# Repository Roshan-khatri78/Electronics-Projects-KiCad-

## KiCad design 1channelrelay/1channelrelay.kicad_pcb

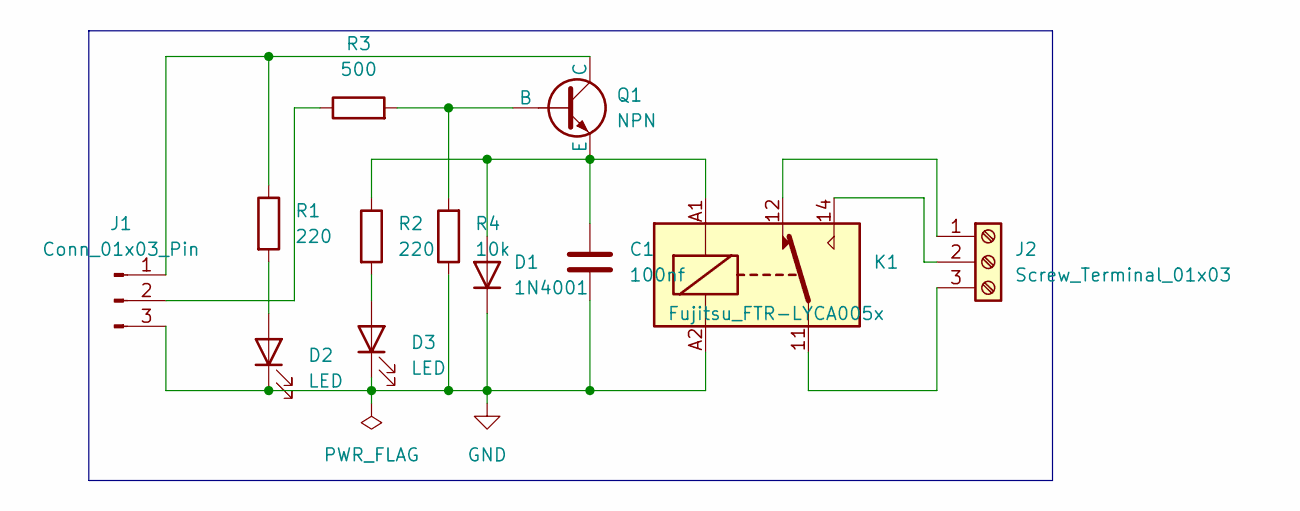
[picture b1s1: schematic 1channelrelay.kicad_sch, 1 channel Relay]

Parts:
C1: 100nf; C_0201_0603Metric
D1: 1N4001; D_0201_0603Metric
D2, D3: LED; LED_0201_0603Metric
J1: Conn_01x03_Pin; PinHeader_1x03_P1.00mm_Horizontal
J2: Screw_Terminal_01x03; TerminalBlock_RND_205-00013_1x03_P5.00mm_Horizontal
K1: Fujitsu_FTR-LYCA005x; Relay_SPDT_Finder_36.11
Q1: NPN; SOT-23
R1, R2: 220; R_0201_0603Metric
R3: 500; R_0201_0603Metric
R4: 10k; R_0201_0603Metric

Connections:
GND: C1.2, D1.1 (K), D2.1 (K), D3.1 (K), J1.3, K1.A2, R4.1; also elsewhere on the board
unnamed: C1.1, D1.2 (A), K1.A1, Q1.3 (E), R2.1
unnamed: D2.2 (A), R1.2
unnamed: D3.2 (A), R2.2
unnamed 4: J1.1, Q1.1 (C), R1.1; also elsewhere on the board
unnamed 5: J1.2, R3.1; also elsewhere on the board
unnamed: J2.1, K1.12
unnamed: J2.2, K1.14
unnamed: J2.3, K1.11
unnamed: Q1.2 (B), R3.2, R4.2

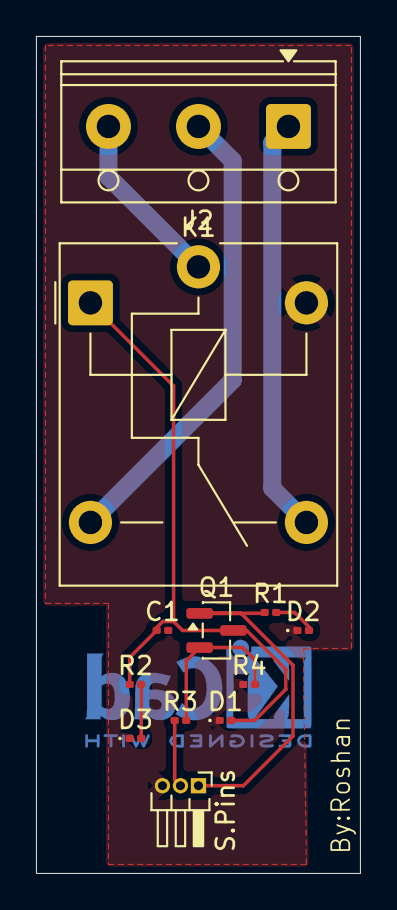
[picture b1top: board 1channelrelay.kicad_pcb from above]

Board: 2 copper layers, 18.0 x 46.5 mm, 12 parts (0 on the bottom side), 10 nets.

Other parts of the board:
S.Pins: Conn_01x03_Pin; PinHeader_1x03_P1.00mm_Horizontal

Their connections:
GND: S.Pins.3; also elsewhere on the board
unnamed 4: S.Pins.1; also elsewhere on the board
unnamed 5: S.Pins.2; also elsewhere on the board

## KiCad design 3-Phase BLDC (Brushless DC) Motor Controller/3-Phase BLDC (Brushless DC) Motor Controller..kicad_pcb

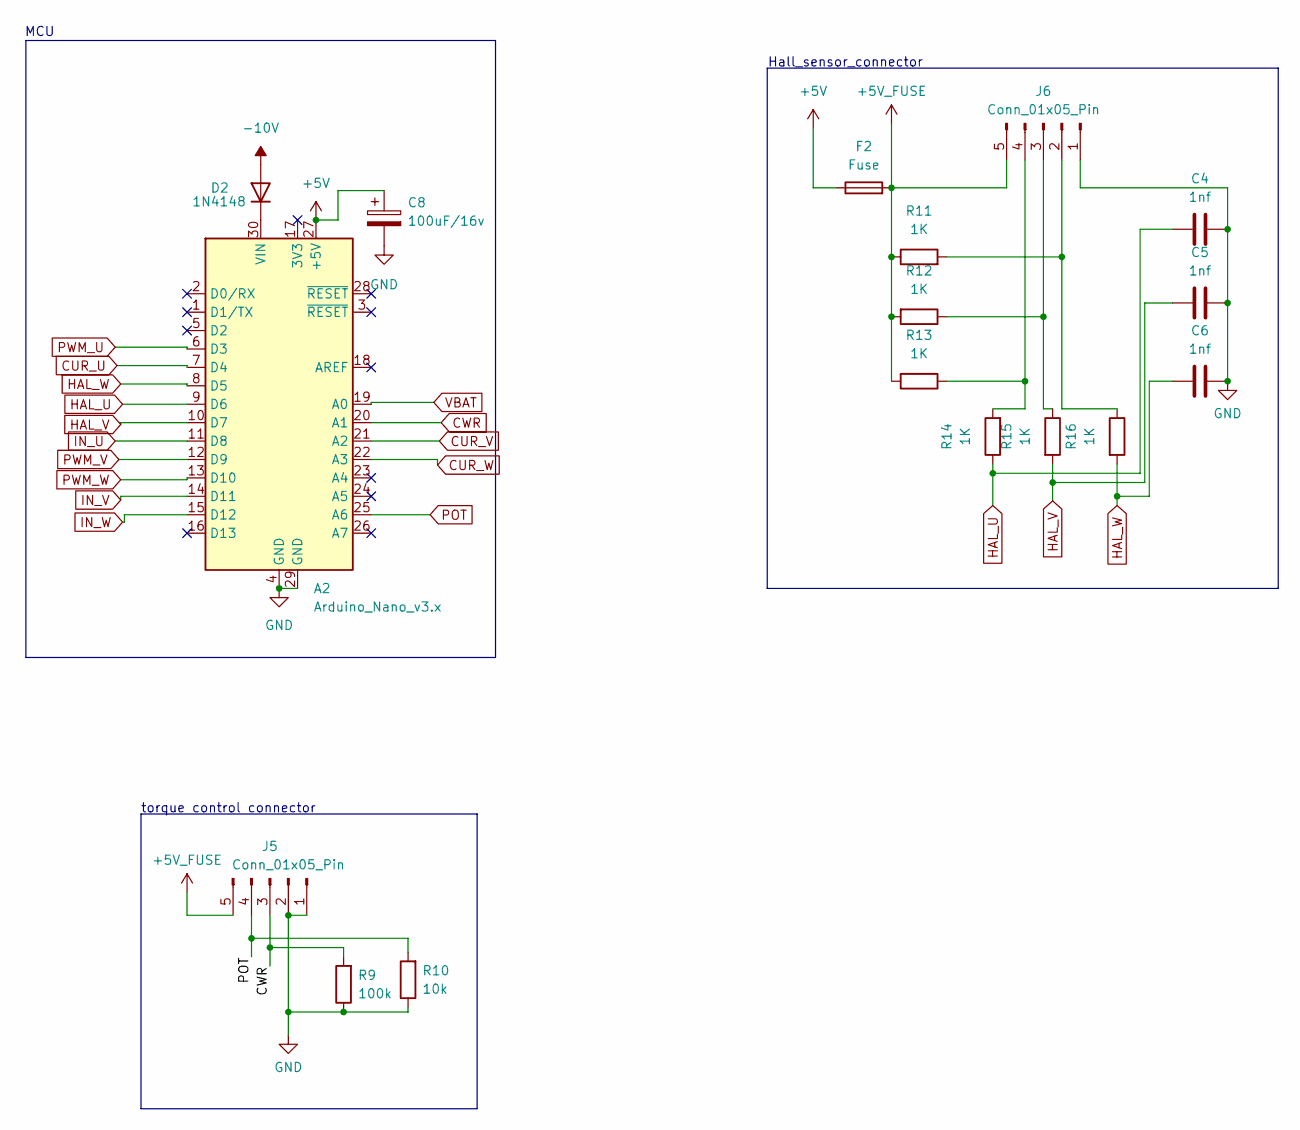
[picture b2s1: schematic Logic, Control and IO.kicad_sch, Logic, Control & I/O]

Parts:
A2: Arduino_Nano_v3.x; Arduino_Nano
C4, C5, C6: 1nf; C_Disc_D5.0mm_W2.5mm_P2.50mm
C8: 100uF/16v; CP_Radial_D5.0mm_P2.50mm
D2: 1N4148; D_DO-35_SOD27_P7.62mm_Horizontal
F2: Fuse; Fuse_2010_5025Metric
J5, J6: Conn_01x05_Pin; PinHeader_1x05_P2.54mm_Vertical
R9: 100k; R_Axial_DIN0204_L3.6mm_D1.6mm_P5.08mm_Horizontal
R10: 10k; R_Axial_DIN0204_L3.6mm_D1.6mm_P5.08mm_Horizontal
R11, R12, R13, R14, R15, R16: 1K; R_Axial_DIN0204_L3.6mm_D1.6mm_P5.08mm_Horizontal

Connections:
+5V: A2.27 (+5V), C8.1, F2.1; also elsewhere on the board
+5V_FUSE: F2.2, J5.5, J6.5, R11.1, R12.2, R13.2
-10V: D2.2 (A); also elsewhere on the board
CUR_U: A2.7 (D4); also elsewhere on the board
CUR_V: A2.21 (A2); also elsewhere on the board
CUR_W: A2.22 (A3); also elsewhere on the board
CWR: A2.20 (A1), J5.3, R9.2
GND: A2.4 (GND), A2.29 (GND), C4.2, C5.2, C6.2, C8.2, J5.1, J5.2, J6.1, R9.1, R10.1; also elsewhere on the board
HAL_U: A2.9 (D6), C4.1, R14.1
HAL_V: A2.10 (D7), C5.1, R15.2
HAL_W: A2.8 (D5), C6.1, R16.2
IN_U: A2.11 (D8); also elsewhere on the board
IN_V: A2.14 (D11); also elsewhere on the board
IN_W: A2.15 (D12); also elsewhere on the board
unnamed: A2.30 (VIN), D2.1 (K)
unnamed: J6.2, R11.2, R16.1
unnamed: J6.3, R12.1, R15.1
unnamed: J6.4, R13.1, R14.2
POT: A2.25 (A6), J5.4, R10.2
PWM_U: A2.6 (D3); also elsewhere on the board
PWM_V: A2.12 (D9); also elsewhere on the board
PWM_W: A2.13 (D10); also elsewhere on the board
VBAT: A2.19 (A0); also elsewhere on the board

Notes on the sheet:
torque control connector
MCU
Hall_sensor_connector

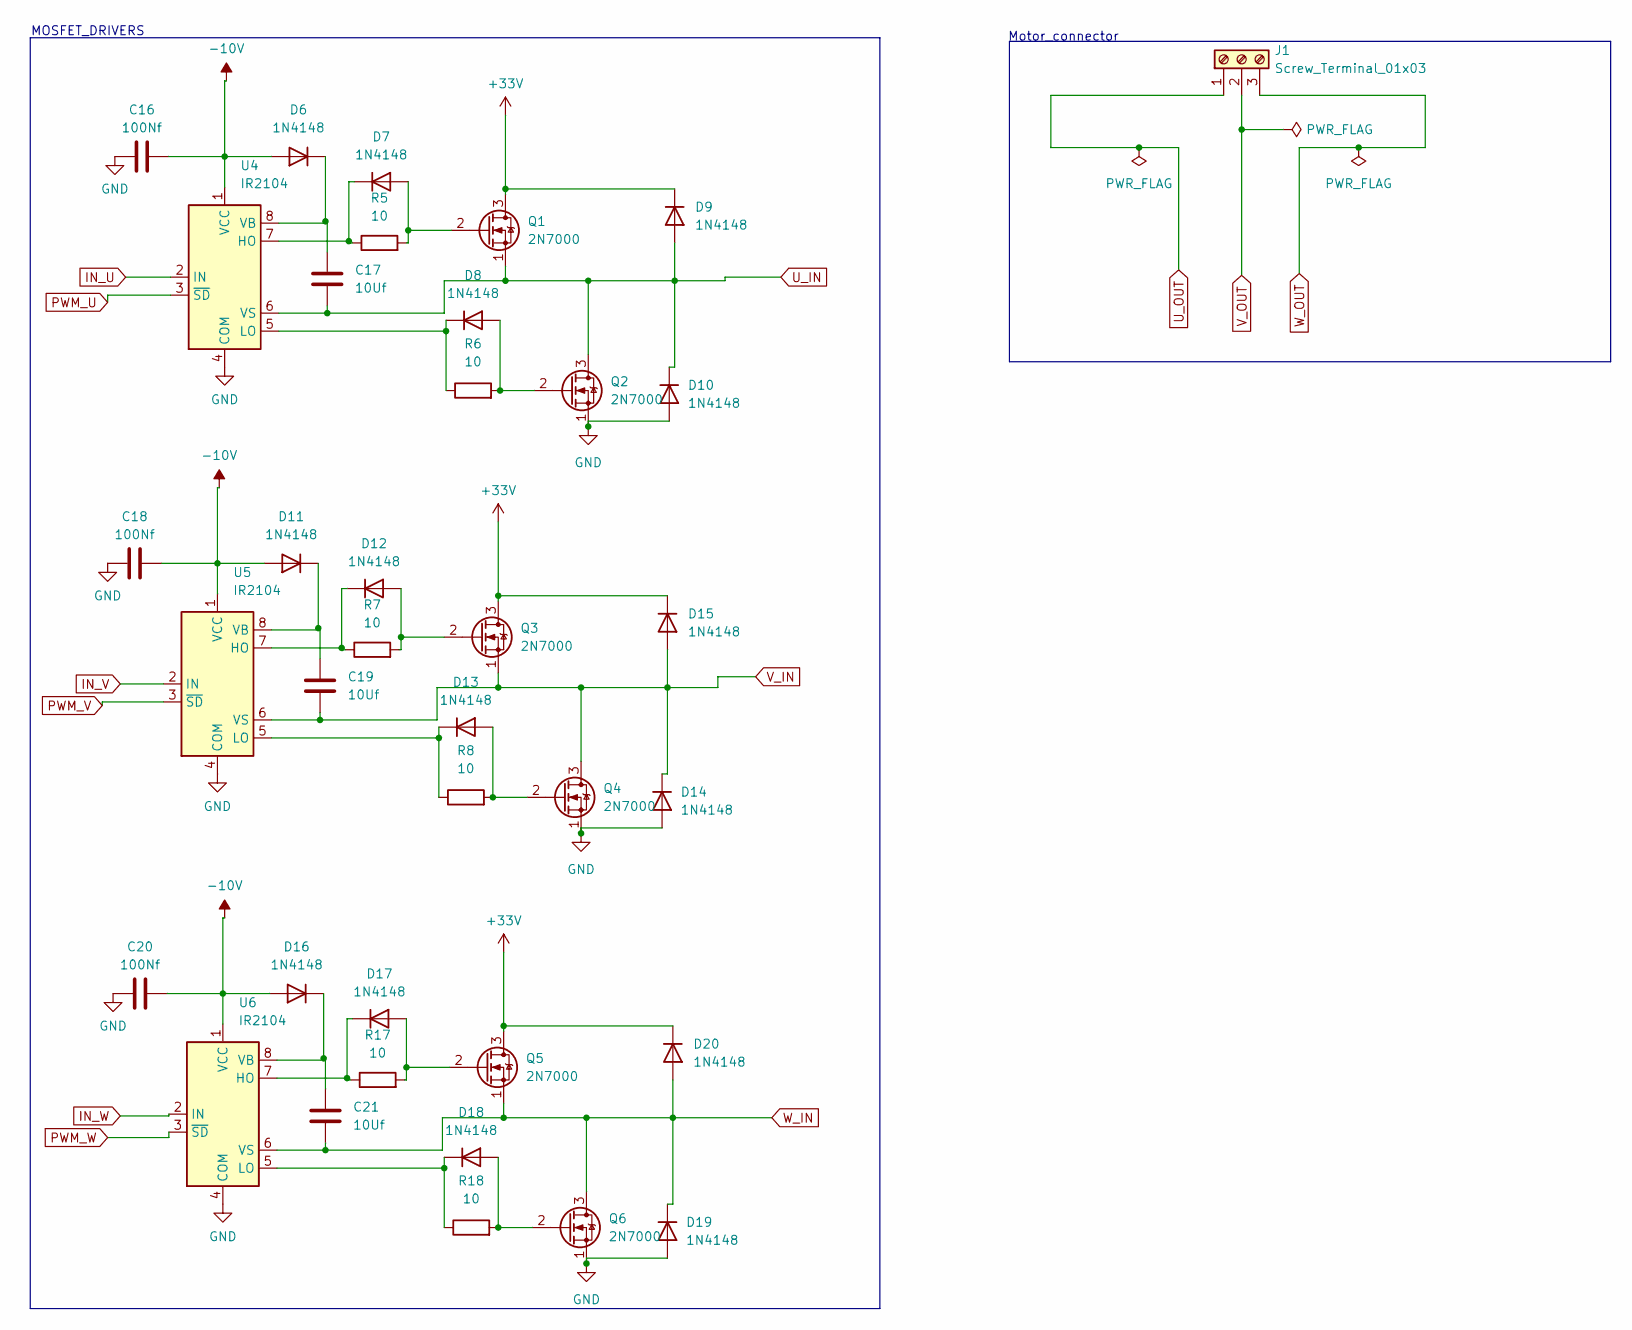
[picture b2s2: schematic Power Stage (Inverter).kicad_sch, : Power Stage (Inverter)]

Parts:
C16, C18, C20: 100Nf; C_Disc_D5.0mm_W2.5mm_P2.50mm
C17, C19, C21: 10Uf; C_Disc_D5.0mm_W2.5mm_P2.50mm
D6, D7, D8, D9, D10, D11, D12, D13, D14, D15, D16, D17, D18, D19, D20: 1N4148; D_DO-35_SOD27_P7.62mm_Horizontal
J1: Screw_Terminal_01x03; TerminalBlock_MaiXu_MX126-5.0-03P_1x03_P5.00mm
Q1, Q2, Q3, Q4, Q5, Q6: 2N7000; TO-92_Inline
R5, R6, R7, R8: 10; R_Axial_DIN0204_L3.6mm_D1.6mm_P1.90mm_Vertical
R17, R18: 10; R_Axial_DIN0204_L3.6mm_D1.6mm_P5.08mm_Horizontal
U4, U5, U6: IR2104; SOIC-8_3.9x4.9mm_P1.27mm

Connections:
+33V: D9.1 (K), D15.1 (K), D20.1 (K), Q1.3 (D), Q3.3 (D), Q5.3 (D); also elsewhere on the board
-10V: C16.2, C18.2, C20.2, D6.2 (A), D11.2 (A), D16.2 (A), U4.1 (VCC), U5.1 (VCC), U6.1 (VCC); also elsewhere on the board
GND: C16.1, C18.1, C20.1, D10.2 (A), D14.2 (A), D19.2 (A), Q2.1 (S), Q4.1 (S), Q6.1 (S), U4.4 (COM), U5.4 (COM), U6.4 (COM); also elsewhere on the board
IN_U: U4.2 (IN); also elsewhere on the board
IN_V: U5.2 (IN); also elsewhere on the board
IN_W: U6.2 (IN); also elsewhere on the board
unnamed: C17.1, D6.1 (K), U4.8 (VB)
unnamed: D7.2 (A), Q1.2 (G), R5.2
unnamed: D7.1 (K), R5.1, U4.7 (HO)
unnamed: D8.2 (A), Q2.2 (G), R6.2
unnamed: D8.1 (K), R6.1, U4.5 (LO)
unnamed: C19.1, D11.1 (K), U5.8 (VB)
unnamed: D12.2 (A), Q3.2 (G), R7.2
unnamed: D12.1 (K), R7.1, U5.7 (HO)
unnamed: D13.2 (A), Q4.2 (G), R8.2
unnamed: D13.1 (K), R8.1, U5.5 (LO)
unnamed: C21.1, D16.1 (K), U6.8 (VB)
unnamed: D17.2 (A), Q5.2 (G), R17.2
unnamed: D17.1 (K), R17.1, U6.7 (HO)
unnamed: D18.2 (A), Q6.2 (G), R18.2
unnamed: D18.1 (K), R18.1, U6.5 (LO)
PWM_U: U4.3 (~SD); also elsewhere on the board
PWM_V: U5.3 (~SD); also elsewhere on the board
PWM_W: U6.3 (~SD); also elsewhere on the board
U_IN: C17.2, D9.2 (A), D10.1 (K), Q1.1 (S), Q2.3 (D), U4.6 (VS); also elsewhere on the board
U_OUT: J1.1; also elsewhere on the board
V_IN: C19.2, D14.1 (K), D15.2 (A), Q3.1 (S), Q4.3 (D), U5.6 (VS); also elsewhere on the board
V_OUT: J1.2; also elsewhere on the board
W_IN: C21.2, D19.1 (K), D20.2 (A), Q5.1 (S), Q6.3 (D), U6.6 (VS); also elsewhere on the board
W_OUT: J1.3; also elsewhere on the board

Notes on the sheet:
Motor_connector
MOSFET_DRIVERS

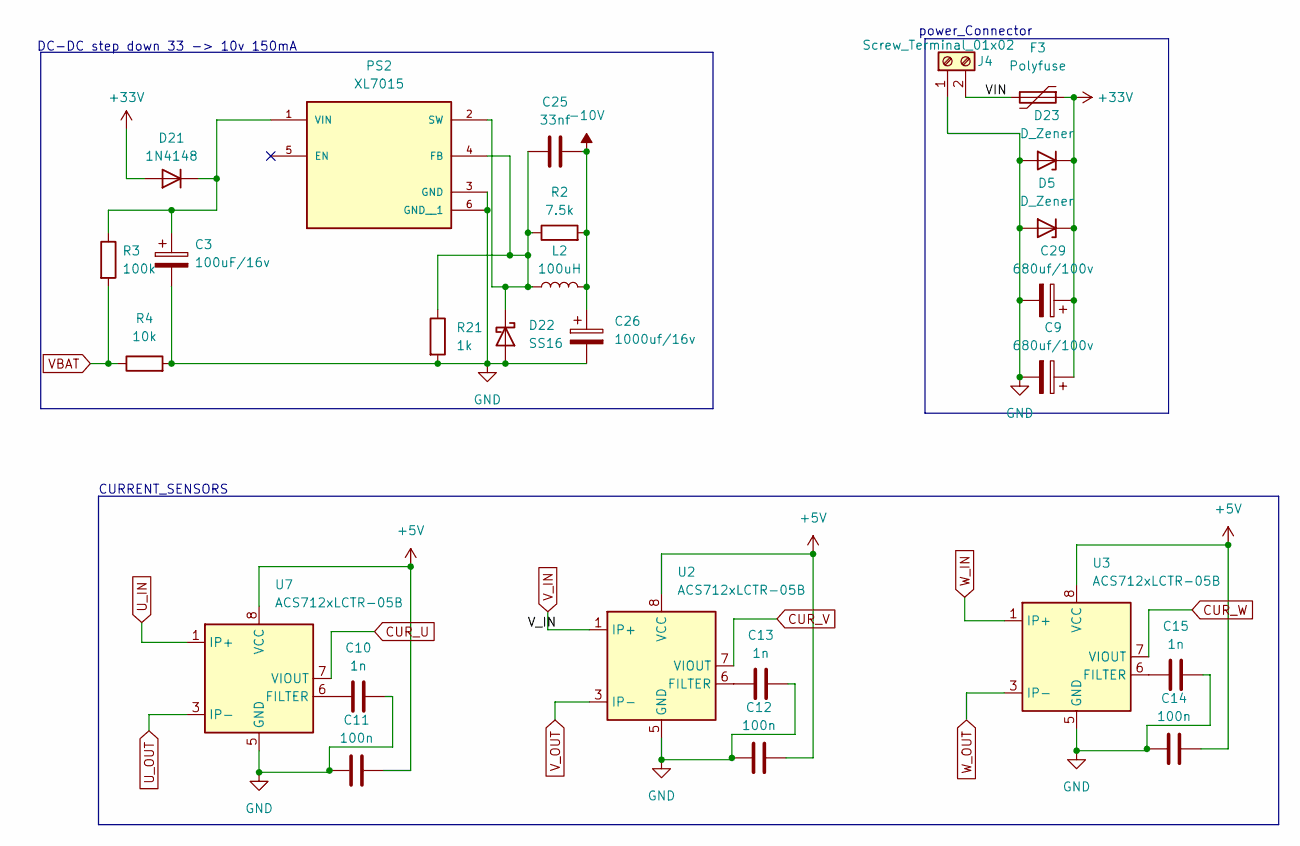
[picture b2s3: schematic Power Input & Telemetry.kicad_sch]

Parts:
C3: 100uF/16v; CP_Radial_D5.0mm_P2.50mm
C9, C29: 680uf/100v; CP_Radial_D5.0mm_P2.50mm
C10, C13, C15: 1n; C_Disc_D5.0mm_W2.5mm_P2.50mm
C11, C12, C14: 100n; C_Disc_D5.0mm_W2.5mm_P2.50mm
C25: 33nf; C_Disc_D5.0mm_W2.5mm_P2.50mm
C26: 1000uf/16v; CP_Radial_D5.0mm_P2.50mm
D5: D_Zener; D_DO-15_P12.70mm_Horizontal
D21: 1N4148; D_DO-35_SOD27_P7.62mm_Horizontal
D22: SS16; D_SMA
D23: D_Zener; D_A-405_P10.16mm_Horizontal
F3: Polyfuse; Fuse_0805_2012Metric
J4: Screw_Terminal_01x02; TerminalBlock_MaiXu_MX126-5.0-02P_1x02_P5.00mm
L2: 100uH; L_Axial_L5.0mm_D3.6mm_P10.00mm_Horizontal_Murata_BL01RN1A2A2
PS2: XL7015; CONV_XL7015; PARTREV 1.8
R2: 7.5k; R_Axial_DIN0204_L3.6mm_D1.6mm_P1.90mm_Vertical
R3: 100k; R_Axial_DIN0204_L3.6mm_D1.6mm_P1.90mm_Vertical
R4: 10k; R_Axial_DIN0204_L3.6mm_D1.6mm_P1.90mm_Vertical
R21: 1k; R_Axial_DIN0204_L3.6mm_D1.6mm_P5.08mm_Horizontal
U2, U3, U7: ACS712xLCTR-05B; SOIC-8_3.9x4.9mm_P1.27mm

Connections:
+5V: C11.2, C12.2, C14.2, U2.8 (VCC), U3.8 (VCC), U7.8 (VCC); also elsewhere on the board
+33V: C9.1, C29.1, D5.1 (K), D21.2 (A), D23.1 (K), F3.1; also elsewhere on the board
-10V: C25.2, C26.1, L2.2, R2.2; also elsewhere on the board
/Power Input & Telemetry/VIN: F3.2, J4.2
CUR_U: U7.7 (VIOUT); also elsewhere on the board
CUR_V: U2.7 (VIOUT); also elsewhere on the board
CUR_W: U3.7 (VIOUT); also elsewhere on the board
GND: C3.2, C9.2, C10.2, C11.1, C12.1, C13.2, C14.1, C15.2, C26.2, C29.2, D5.2 (A), D22.2 (A), D23.2 (A), J4.1, PS2.3 (GND), PS2.6 (GND__1), R4.2, R21.2, U2.5 (GND), U3.5 (GND), U7.5 (GND); also elsewhere on the board
unnamed: C3.1, D21.1 (K), PS2.1 (VIN), R3.1
unnamed: C25.1, D22.1 (K), L2.1, PS2.2 (SW), PS2.4 (FB), R2.1, R21.1
unnamed: C13.1, U2.6 (FILTER)
unnamed: C15.1, U3.6 (FILTER)
unnamed: C10.1, U7.6 (FILTER)
U_IN: U7.1 (IP+), U7.2 (IP+); also elsewhere on the board
U_OUT: U7.3 (IP-), U7.4 (IP-); also elsewhere on the board
VBAT: R3.2, R4.1; also elsewhere on the board
V_IN: U2.1 (IP+), U2.2 (IP+); also elsewhere on the board
V_OUT: U2.3 (IP-), U2.4 (IP-); also elsewhere on the board
W_IN: U3.1 (IP+), U3.2 (IP+); also elsewhere on the board
W_OUT: U3.3 (IP-), U3.4 (IP-); also elsewhere on the board

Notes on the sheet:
CURRENT_SENSORS
DC-DC step down 33 -> 10v 150mA
power_Connector

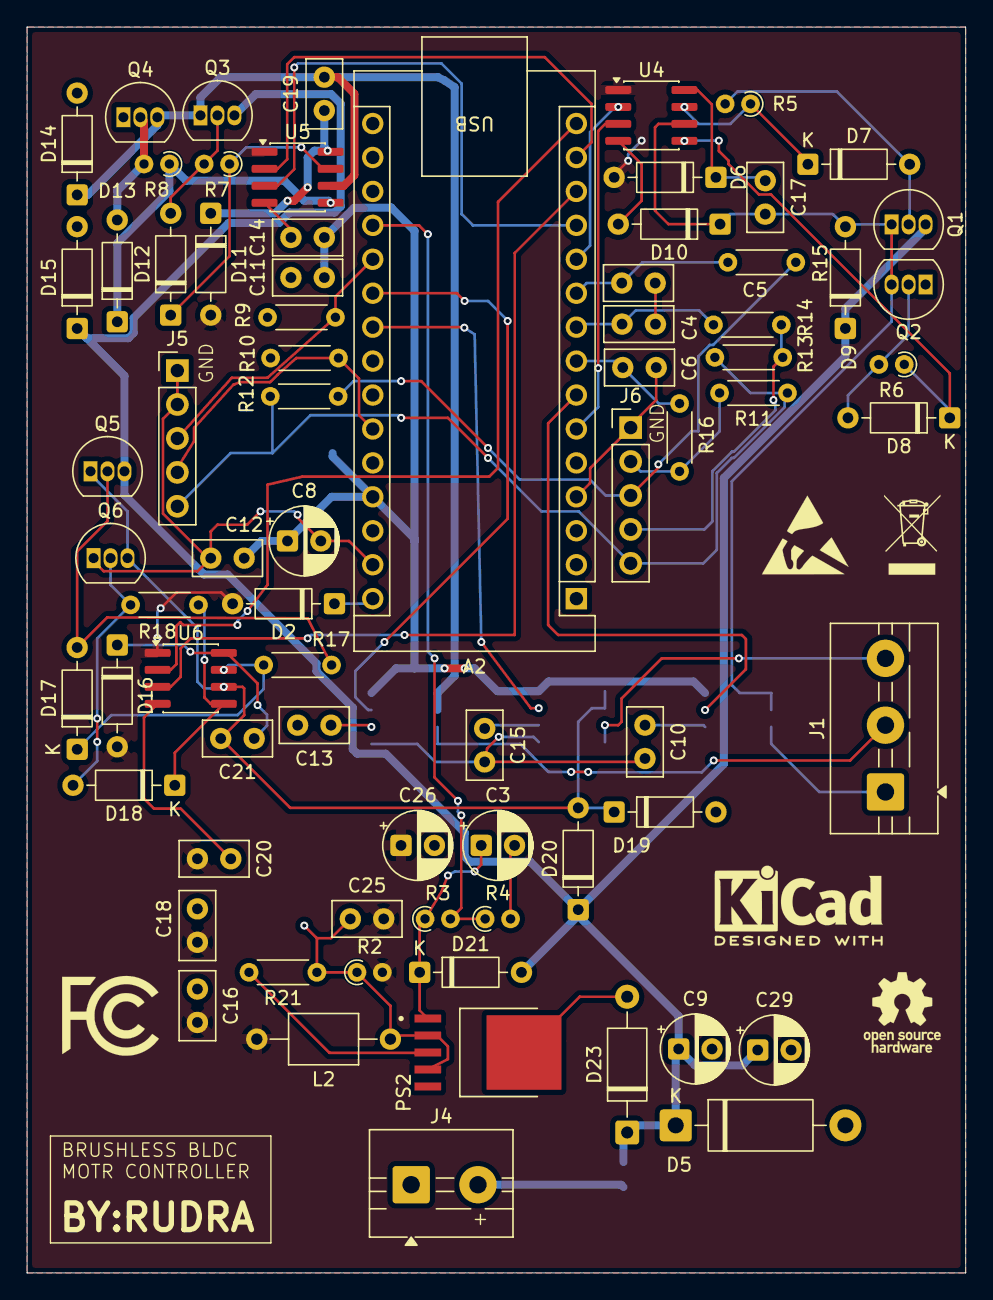
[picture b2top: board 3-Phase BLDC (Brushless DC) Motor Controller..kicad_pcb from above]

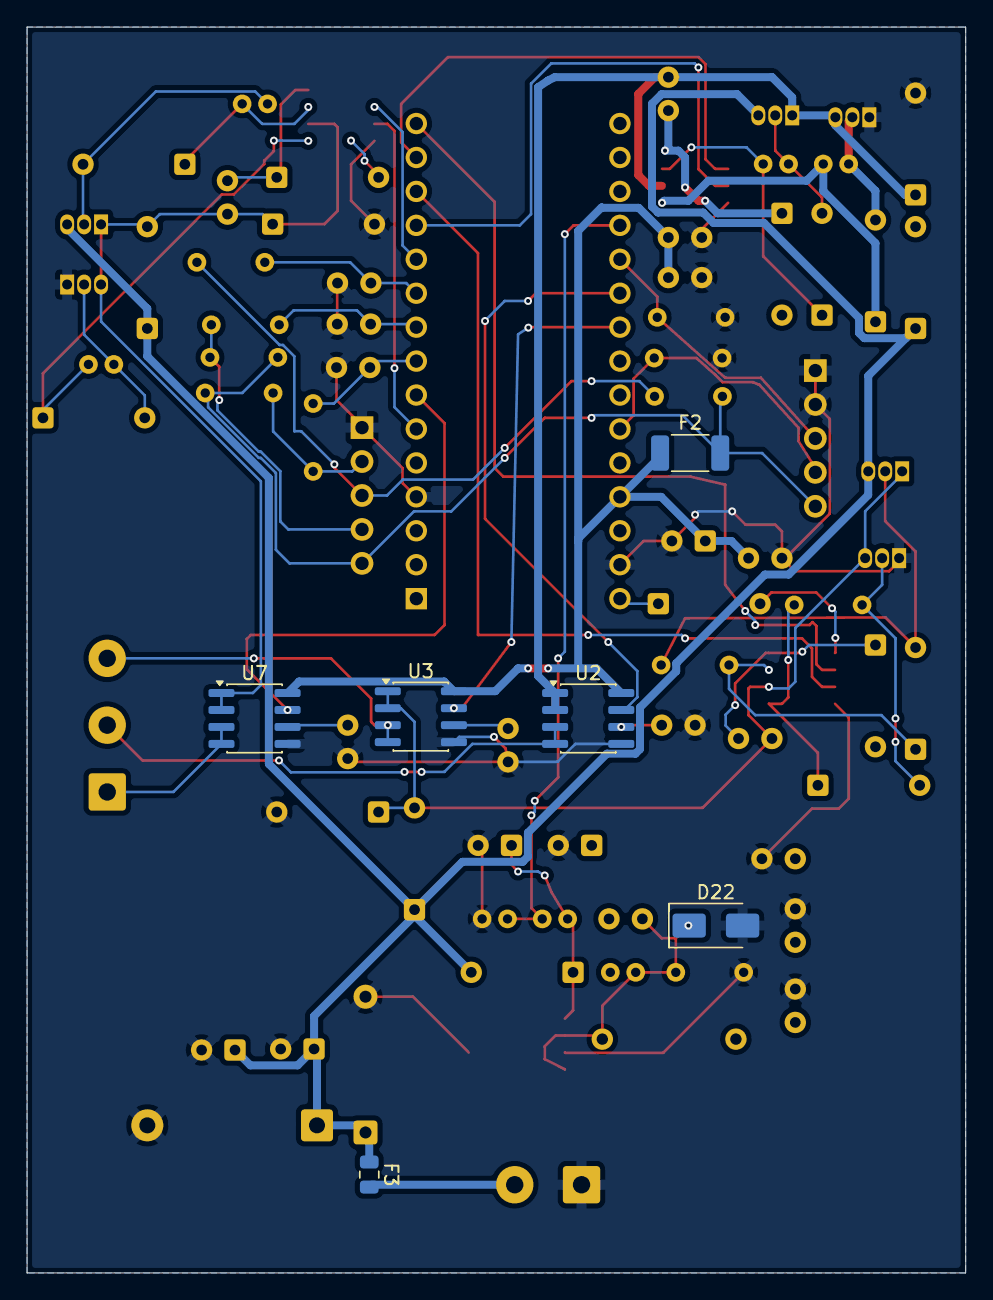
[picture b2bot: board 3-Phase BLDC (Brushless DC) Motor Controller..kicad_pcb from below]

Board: 4 copper layers, 70.2 x 93.2 mm, 80 parts (6 on the bottom side), 51 nets.

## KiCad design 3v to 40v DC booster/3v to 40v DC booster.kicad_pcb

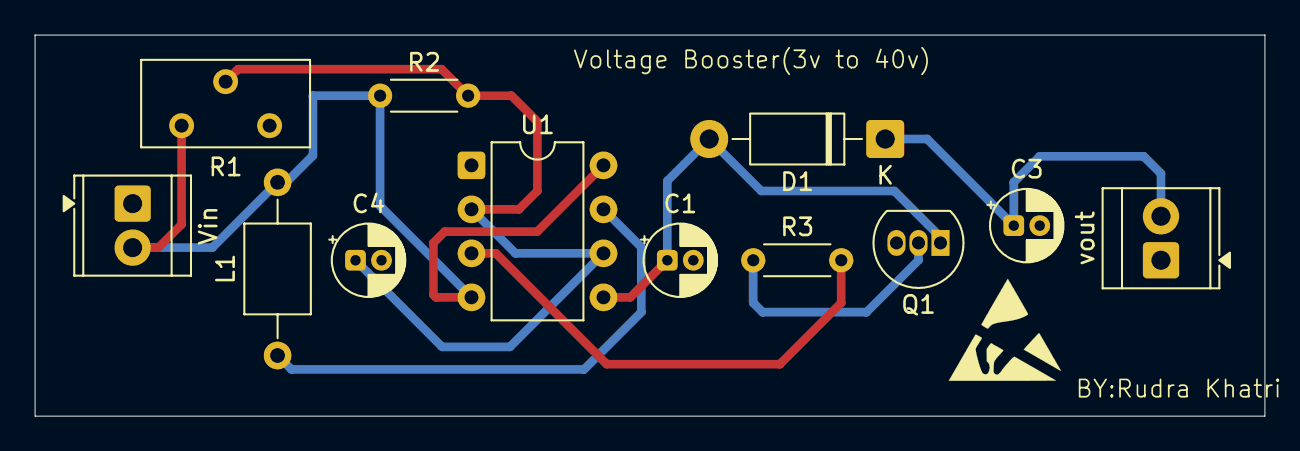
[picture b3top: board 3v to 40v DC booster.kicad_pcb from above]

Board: 2 copper layers, 71.0 x 22.0 mm, 12 parts (0 on the bottom side), 8 nets.

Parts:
C1: 0.01uf; CP_Radial_D4.0mm_P1.50mm
C3: C_Polarized_US; CP_Radial_D4.0mm_P1.50mm
C4: 470pf; CP_Radial_D4.0mm_P1.50mm
D1: 1N4006; D_DO-41_SOD81_P10.16mm_Horizontal
L1: L; L_Axial_L5.0mm_D3.6mm_P10.00mm_Horizontal_Murata_BL01RN1A2A2
Q1: BC547; TO-92_Inline
R1: Potentiometer; Potentiometer_Bourns_3296Y_Vertical
R2, R3: 1k; R_Axial_DIN0204_L3.6mm_D1.6mm_P5.08mm_Horizontal
U1: LM555xN; DIP-8_W7.62mm
Vin: Screw_Terminal_01x02; TerminalBlock_TE_282834-2_1x02_P2.54mm_Horizontal
vout: Screw_Terminal_01x02; TerminalBlock_TE_282834-2_1x02_P2.54mm_Horizontal

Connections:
GND: C1.2, C3.2, C4.2, Q1.3 (E), R1.3, U1.1 (GND), Vin.1, vout.1
unnamed: C1.1, D1.2 (A), Q1.1 (C), U1.5 (CONT)
unnamed: C3.1, D1.1 (K), vout.2
unnamed: L1.2, R1.1, R2.1, U1.4 (~RST), U1.8 (VCC), Vin.2
unnamed: Q1.2 (B), R3.1
unnamed: L1.1, U1.7 (DISCH)
unnamed: R3.2, U1.3 (OUT)
unnamed: C4.1, R1.2, R2.2, U1.2 (TRIG), U1.6 (THRES)

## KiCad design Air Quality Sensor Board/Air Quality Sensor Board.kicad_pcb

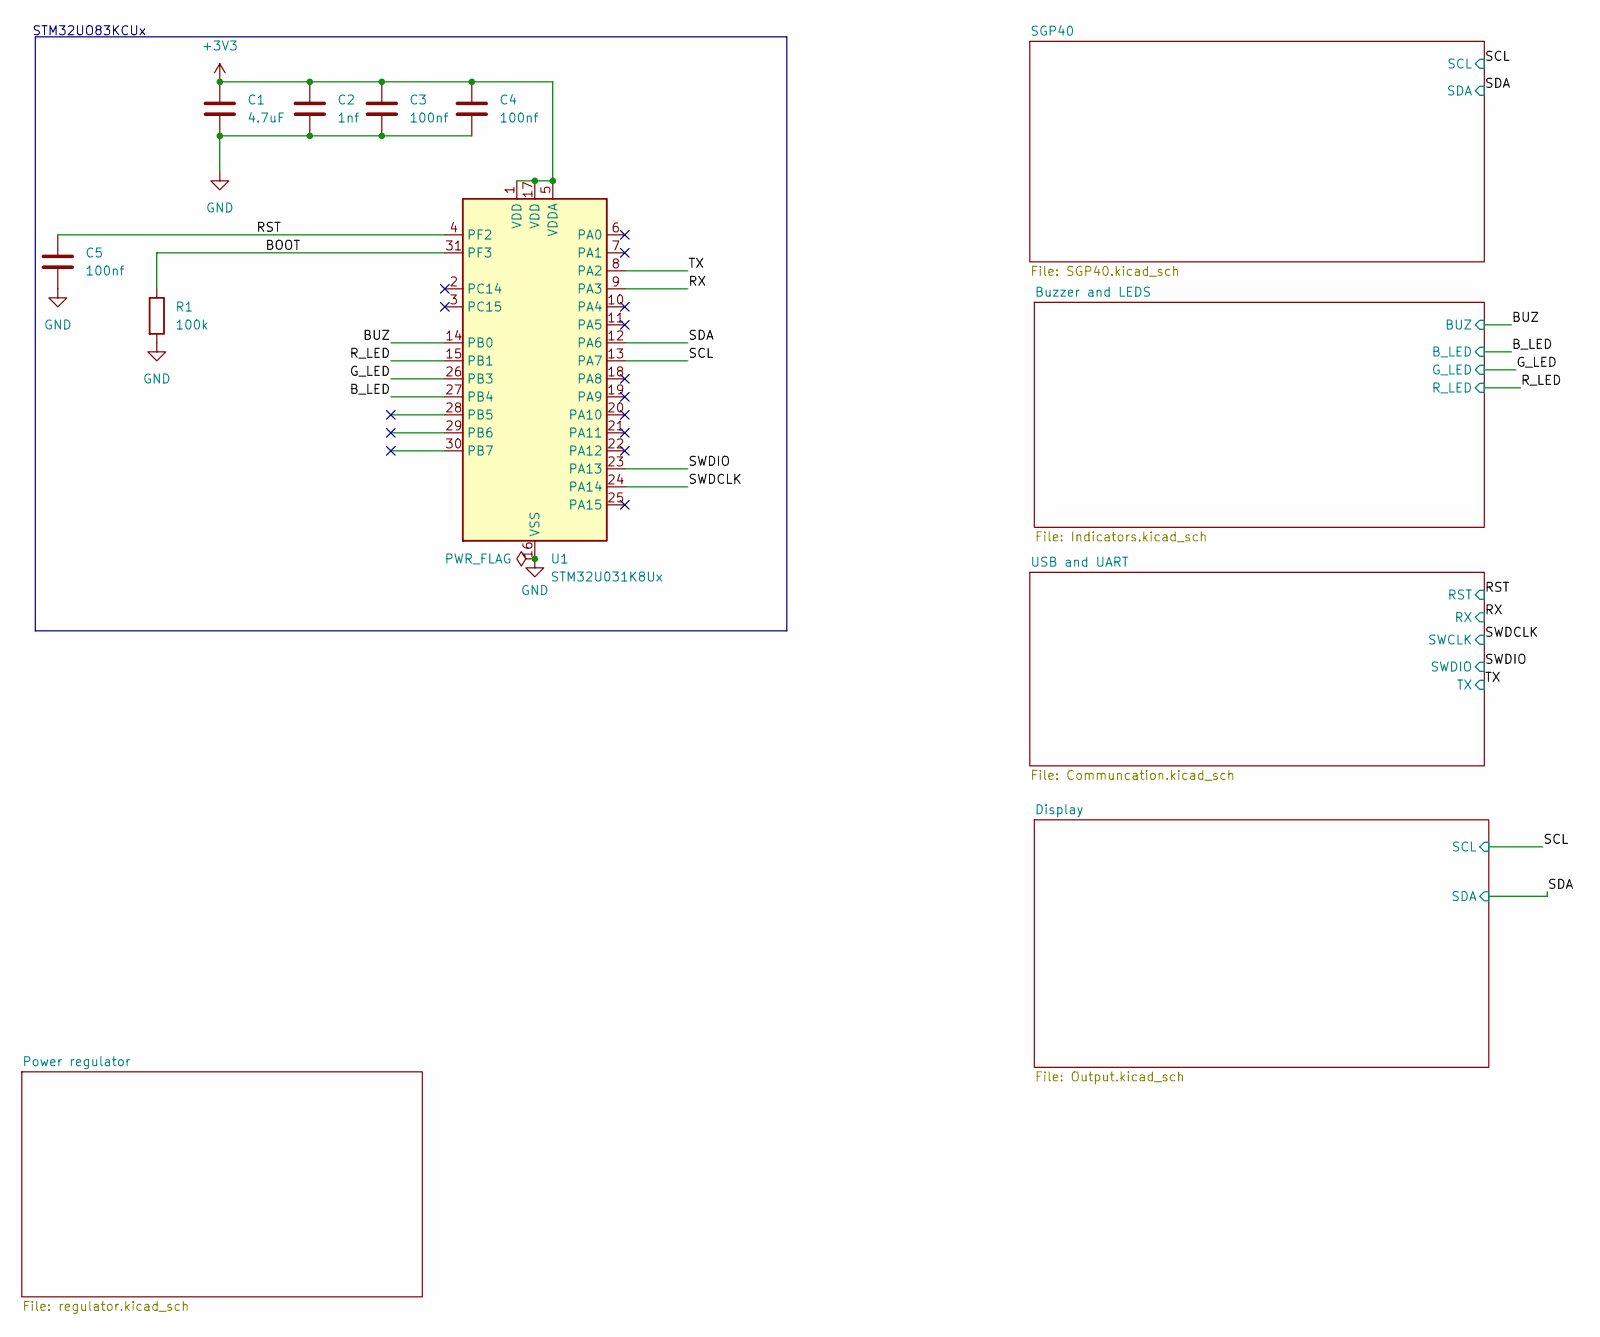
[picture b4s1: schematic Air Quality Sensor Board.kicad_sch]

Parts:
C1: 4.7uF; C_0805_2012Metric
C2: 1nf; C_0805_2012Metric
C3, C4, C5: 100nf; C_0805_2012Metric
R1: 100k; R_0805_2012Metric
U1: STM32U031K8Ux; QFN-32-1EP_5x5mm_P0.5mm_EP3.45x3.45mm

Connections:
+3V3: C1.1, C2.1, C3.1, C4.1, U1.1 (VDD), U1.5 (VDDA), U1.17 (VDD); also elsewhere on the board
/BOOT: R1.1, U1.31 (PF3)
/BUZ: U1.14 (PB0); also elsewhere on the board
/B_LED: U1.27 (PB4); also elsewhere on the board
/G_LED: U1.26 (PB3); also elsewhere on the board
/RST: C5.1, U1.4 (PF2); also elsewhere on the board
/RX: U1.9 (PA3); also elsewhere on the board
/R_LED: U1.15 (PB1); also elsewhere on the board
/SCL: U1.13 (PA7); also elsewhere on the board
/SDA: U1.12 (PA6); also elsewhere on the board
/SWDCLK: U1.24 (PA14); also elsewhere on the board
/SWDIO: U1.23 (PA13); also elsewhere on the board
/TX: U1.8 (PA2); also elsewhere on the board
GND: C1.2, C2.2, C3.2, C4.2, C5.2, R1.2, U1.16 (VSS), U1.32 (VSS), U1.33 (VSS); also elsewhere on the board

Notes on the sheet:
STM32UO83KCUx

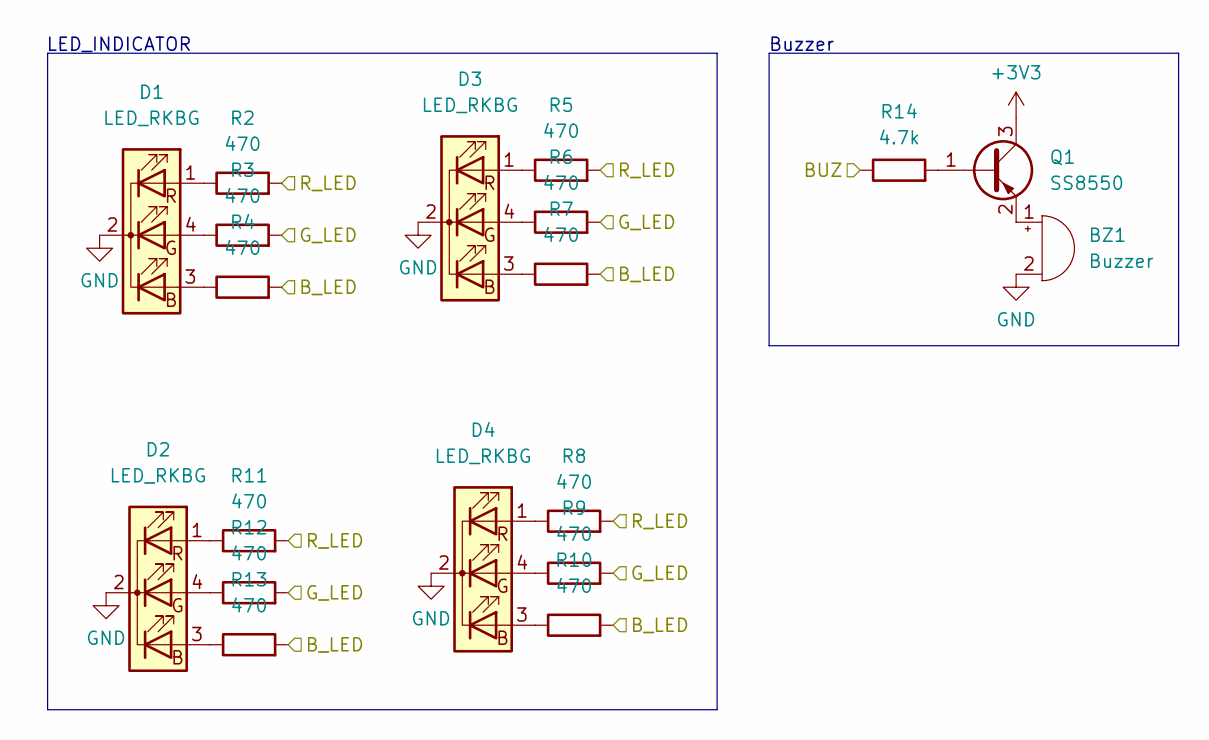
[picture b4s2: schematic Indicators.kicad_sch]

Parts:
BZ1: Buzzer; Buzzer_12x9.5RM7.6
D1, D2, D3, D4: LED_RKBG; LED_RGB_1210
Q1: SS8550; SOT-23
R2, R3, R4, R5, R6, R7, R8, R9, R10, R11, R12, R13: 470; R_0805_2012Metric
R14: 4.7k; R_0805_2012Metric

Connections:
+3V3: Q1.3 (C); also elsewhere on the board
/BUZ: R14.1; also elsewhere on the board
/B_LED: R4.2, R7.2, R10.2, R13.2; also elsewhere on the board
/G_LED: R3.2, R6.2, R9.2, R12.2; also elsewhere on the board
/R_LED: R2.2, R5.2, R8.2, R11.2; also elsewhere on the board
GND: BZ1.2 (-), D1.2 (K), D2.2 (K), D3.2 (K), D4.2 (K); also elsewhere on the board
unnamed: BZ1.1 (+), Q1.2 (E)
unnamed: D1.3 (BA), R4.1
unnamed: D1.4 (GA), R3.1
unnamed: D1.1 (RA), R2.1
unnamed: D2.3 (BA), R13.1
unnamed: D2.4 (GA), R12.1
unnamed: D2.1 (RA), R11.1
unnamed: D3.3 (BA), R7.1
unnamed: D3.4 (GA), R6.1
unnamed: D3.1 (RA), R5.1
unnamed: D4.3 (BA), R10.1
unnamed: D4.4 (GA), R9.1
unnamed: D4.1 (RA), R8.1
unnamed: Q1.1 (B), R14.2

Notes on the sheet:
LED_INDICATOR
Buzzer

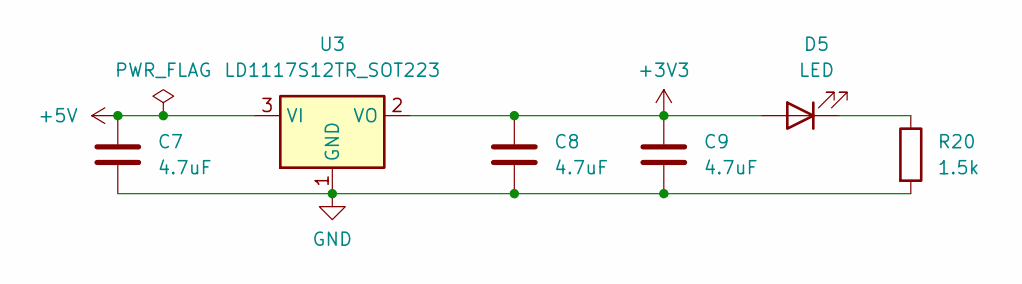
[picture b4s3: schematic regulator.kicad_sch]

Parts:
C7, C8, C9: 4.7uF; C_0805_2012Metric
D5: LED; LED_1210_3225Metric
R20: 1.5k; R_0805_2012Metric
U3: LD1117S12TR_SOT223; SOT-223-3_TabPin2

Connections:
+3V3: C8.1, C9.1, D5.2 (A), U3.2 (VO); also elsewhere on the board
+5V: C7.1, U3.3 (VI); also elsewhere on the board
GND: C7.2, C8.2, C9.2, R20.2, U3.1 (GND); also elsewhere on the board
unnamed: D5.1 (K), R20.1

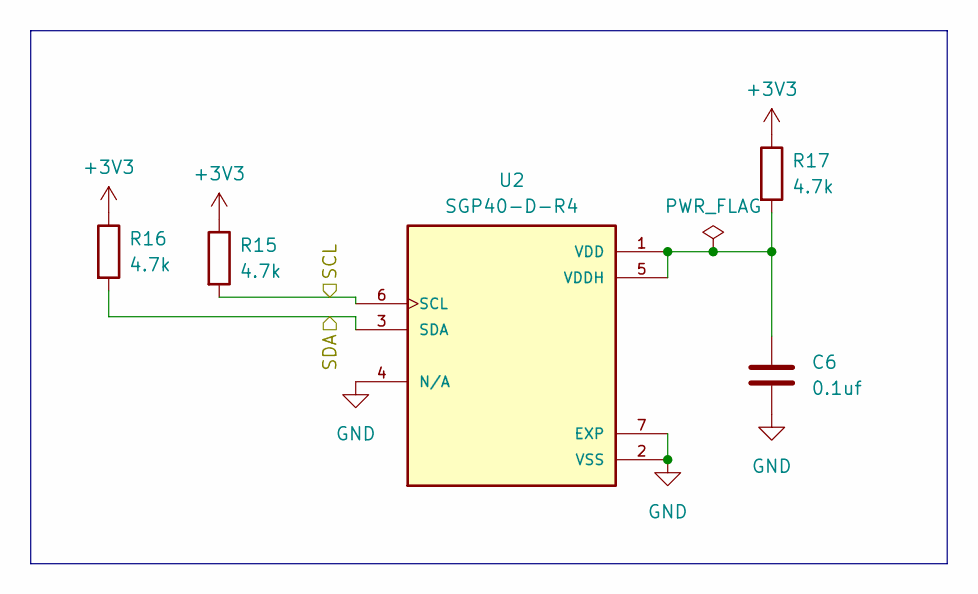
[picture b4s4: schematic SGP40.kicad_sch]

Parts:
C6: 0.1uf; C_0805_2012Metric
R15, R16, R17: 4.7k; R_0805_2012Metric
U2: SGP40-D-R4; XCDR_SGP40-D-R4; PARTREV 1.2

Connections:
+3V3: R15.1, R16.1, R17.1; also elsewhere on the board
/SCL: R15.2, U2.6 (SCL); also elsewhere on the board
/SDA: R16.2, U2.3 (SDA); also elsewhere on the board
GND: C6.2, U2.2 (VSS), U2.4 (N/A), U2.7 (EXP); also elsewhere on the board
unnamed: C6.1, R17.2, U2.1 (VDD), U2.5 (VDDH)

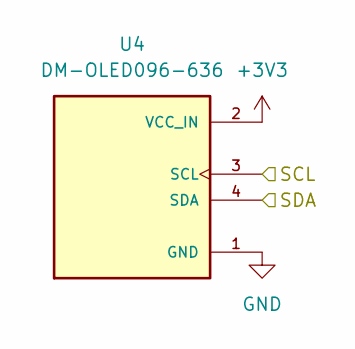
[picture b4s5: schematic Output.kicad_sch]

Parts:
U4: DM-OLED096-636; MODULE_DM-OLED096-636; PARTREV 2018-09-10

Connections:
+3V3: U4.2 (VCC_IN); also elsewhere on the board
/SCL: U4.3 (SCL); also elsewhere on the board
/SDA: U4.4 (SDA); also elsewhere on the board
GND: U4.1 (GND); also elsewhere on the board

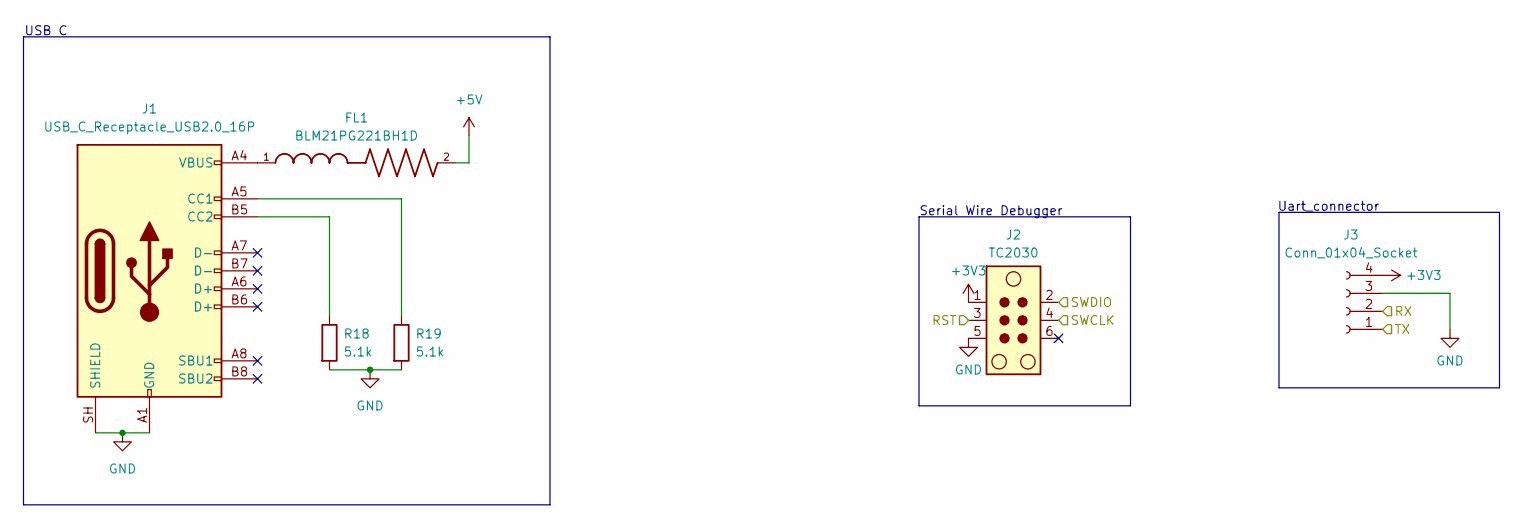
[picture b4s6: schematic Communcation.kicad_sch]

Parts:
FL1: BLM21PG221BH1D; BEADC2012X105N
J1: USB_C_Receptacle_USB2.0_16P; USB_C_Receptacle_Amphenol_12401948E412A
J2: TC2030; Tag-Connect_TC2030-IDC-NL_2x03_P1.27mm_Vertical
J3: Conn_01x04_Socket; PinSocket_1x04_P2.00mm_Vertical
R18, R19: 5.1k; R_0805_2012Metric

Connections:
+3V3: J2.1, J3.4; also elsewhere on the board
+5V: FL1.2; also elsewhere on the board
/RST: J2.3; also elsewhere on the board
/RX: J3.2; also elsewhere on the board
/SWDCLK: J2.4; also elsewhere on the board
/SWDIO: J2.2; also elsewhere on the board
/TX: J3.1; also elsewhere on the board
GND: J1.A1 (GND), J1.A12 (GND), J1.B1 (GND), J1.B12 (GND), J1.SH (SHIELD), J2.5, J3.3, R18.2, R19.2; also elsewhere on the board
unnamed: FL1.1, J1.A4 (VBUS), J1.A9 (VBUS), J1.B4 (VBUS), J1.B9 (VBUS)
unnamed: J1.A5 (CC1), R19.1
unnamed: J1.B5 (CC2), R18.1

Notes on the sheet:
Uart_connector
USB C
Serial Wire Debugger

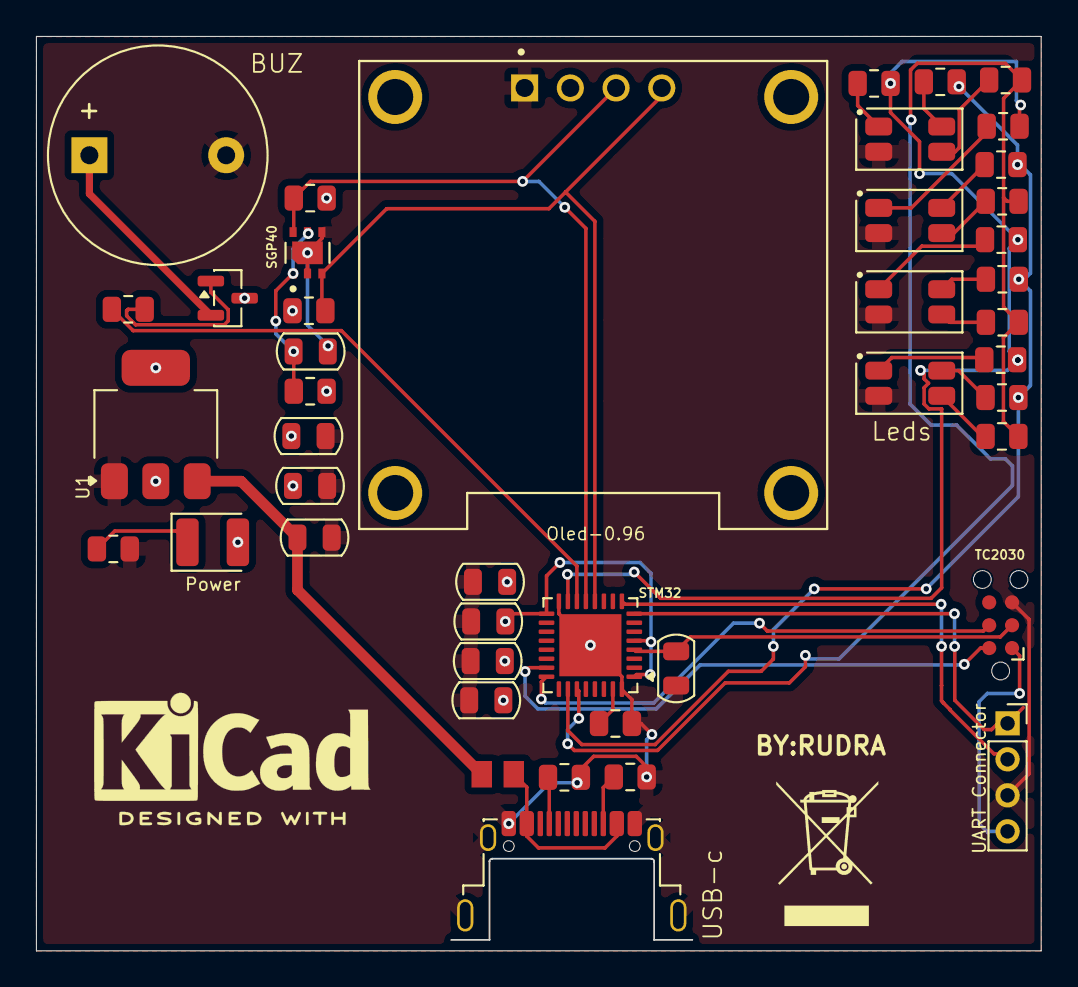
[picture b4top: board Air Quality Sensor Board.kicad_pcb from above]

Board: 4 copper layers, 55.8 x 50.8 mm, 44 parts (0 on the bottom side), 34 nets.
